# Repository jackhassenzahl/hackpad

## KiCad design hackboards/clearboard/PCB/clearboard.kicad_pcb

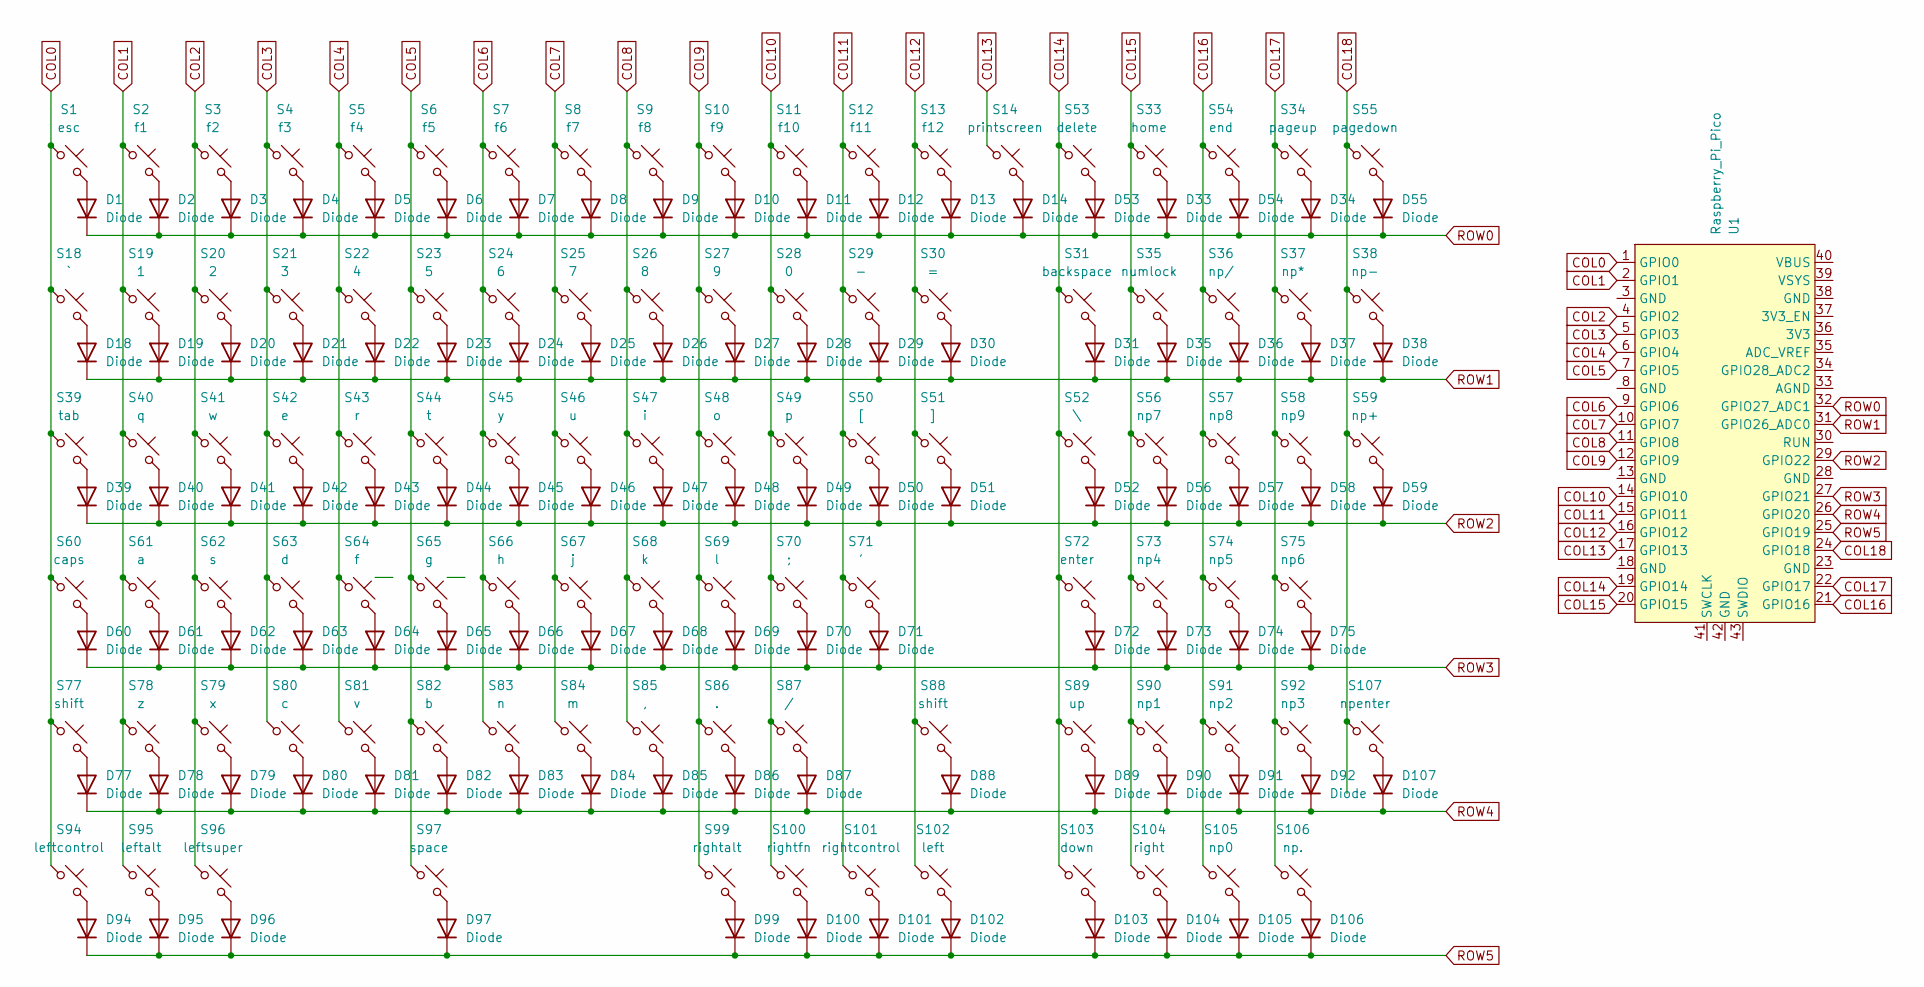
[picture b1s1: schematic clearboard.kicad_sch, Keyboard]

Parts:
D1, D2, D3, D4, D5, D6, D7, D8, D9, D10, D11, D12, D13, D14, D18, D19, D20, D21, D22, D23, D24, D25, D26, D27, D28, D29, D30, D31, D33, D34, D35, D36, D37, D38, D39, D40, D41, D42, D43, D44, D45, D46, D47, D48, D49, D50, D51, D52, D53, D54, D55, D56, D57, D58, D59, D60, D61, D62, D63, D64, D65, D66, D67, D68, D69, D70, D71, D72, D73, D74, D75, D77, D78, D79, D80, D81, D82, D83, D84, D85, D86, D87, D88, D89, D90, D91, D92, D94, D95, D96, D97, D99, D100, D101, D102, D103, D104, D105, D106, D107: Diode; Diode_DO-35
S1: esc; MX_PCB_1.00u
S2: f1; MX_PCB_1.00u
S3: f2; MX_PCB_1.00u
S4: f3; MX_PCB_1.00u
S5: f4; MX_PCB_1.00u
S6: f5; MX_PCB_1.00u
S7: f6; MX_PCB_1.00u
S8: f7; MX_PCB_1.00u
S9: f8; MX_PCB_1.00u
S10: f9; MX_PCB_1.00u
S11: f10; MX_PCB_1.00u
S12: f11; MX_PCB_1.00u
S13: f12; MX_PCB_1.00u
S14: printscreen; MX_PCB_1.00u
S18: `; MX_PCB_1.00u
S19: 1; MX_PCB_1.00u
S20: 2; MX_PCB_1.00u
S21: 3; MX_PCB_1.00u
S22: 4; MX_PCB_1.00u
S23: 5; MX_PCB_1.00u
S24: 6; MX_PCB_1.00u
S25: 7; MX_PCB_1.00u
S26: 8; MX_PCB_1.00u
S27: 9; MX_PCB_1.00u
S28: 0; MX_PCB_1.00u
S29: -; MX_PCB_1.00u
S30: =; MX_PCB_1.00u
S31: backspace; MX_PCB_2.00u
S33: home; MX_PCB_1.00u
S34: pageup; MX_PCB_1.00u
S35: numlock; MX_PCB_1.00u
S36: np/; MX_PCB_1.00u
S37: np*; MX_PCB_1.00u
S38: np-; MX_PCB_1.00u
S39: tab; MX_PCB_1.50u
S40: q; MX_PCB_1.00u
S41: w; MX_PCB_1.00u
S42: e; MX_PCB_1.00u
S43: r; MX_PCB_1.00u
S44: t; MX_PCB_1.00u
S45: y; MX_PCB_1.00u
S46: u; MX_PCB_1.00u
S47: i; MX_PCB_1.00u
S48: o; MX_PCB_1.00u
S49: p; MX_PCB_1.00u
S50: [; MX_PCB_1.00u
S51: ]; MX_PCB_1.00u
S52: \; MX_PCB_1.50u
S53: delete; MX_PCB_1.00u
S54: end; MX_PCB_1.00u
S55: pagedown; MX_PCB_1.00u
S56: np7; MX_PCB_1.00u
S57: np8; MX_PCB_1.00u
S58: np9; MX_PCB_1.00u
S59: np+; MX_PCB_2.00u_90deg
S60: caps; MX_PCB_1.75u
S61: a; MX_PCB_1.00u
S62: s; MX_PCB_1.00u
S63: d; MX_PCB_1.00u
S64: f; MX_PCB_1.00u
S65: g; MX_PCB_1.00u
S66: h; MX_PCB_1.00u
S67: j; MX_PCB_1.00u
S68: k; MX_PCB_1.00u
S69: l; MX_PCB_1.00u
S70: ;; MX_PCB_1.00u
S71: '; MX_PCB_1.00u
S72: enter; MX_PCB_2.25u
S73: np4; MX_PCB_1.00u
S74: np5; MX_PCB_1.00u
S75: np6; MX_PCB_1.00u
S77: shift; MX_PCB_2.25u
S78: z; MX_PCB_1.00u
S79: x; MX_PCB_1.00u
S80: c; MX_PCB_1.00u
S81: v; MX_PCB_1.00u
S82: b; MX_PCB_1.00u
S83: n; MX_PCB_1.00u
S84: m; MX_PCB_1.00u
S85: ,; MX_PCB_1.00u
S86: .; MX_PCB_1.00u
S87: /; MX_PCB_1.00u
S88: shift; MX_PCB_1.75u
S89: up; MX_PCB_1.00u
S90: np1; MX_PCB_1.00u
S91: np2; MX_PCB_1.00u
S92: np3; MX_PCB_1.00u
S94: leftcontrol; MX_Plate_1.25u
S95: leftalt; MX_Plate_1.25u
S96: leftsuper; MX_Plate_1.25u
S97: space; MX_PCB_6.25u
S99: rightalt; MX_PCB_1.00u
S100: rightfn; MX_PCB_1.00u
S101: rightcontrol; MX_PCB_1.00u
S102: left; MX_PCB_1.00u
S103: down; MX_PCB_1.00u
S104: right; MX_PCB_1.00u
S105: np0; MX_PCB_1.00u
S106: np.; MX_PCB_1.00u
S107: npenter; MX_PCB_2.00u_90deg
U1: Raspberry_Pi_Pico

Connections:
COL0: S1.1, S18.1, S39.1, S60.1, S77.1, S94.1, U1.1 (GPIO0)
COL1: S2.1, S19.1, S40.1, S61.1, S78.1, S95.1, U1.2 (GPIO1)
COL2: S3.1, S20.1, S41.1, S62.1, S79.1, S96.1, U1.4 (GPIO2)
COL3: S4.1, S21.1, S42.1, S63.1, S80.1, U1.5 (GPIO3)
COL4: S5.1, S22.1, S43.1, S64.1, S81.1, U1.6 (GPIO4)
COL5: S6.1, S23.1, S44.1, S65.1, S82.1, S97.1, U1.7 (GPIO5)
COL6: S7.1, S24.1, S45.1, S66.1, S83.1, U1.9 (GPIO6)
COL7: S8.1, S25.1, S46.1, S67.1, S84.1, U1.10 (GPIO7)
COL8: S9.1, S26.1, S47.1, S68.1, S85.1, U1.11 (GPIO8)
COL9: S10.1, S27.1, S48.1, S69.1, S86.1, S99.1, U1.12 (GPIO9)
COL10: S11.1, S28.1, S49.1, S70.1, S87.1, S100.1, U1.14 (GPIO10)
COL11: S12.1, S29.1, S50.1, S71.1, S101.1, U1.15 (GPIO11)
COL12: S13.1, S30.1, S51.1, S88.1, S102.1, U1.16 (GPIO12)
COL13: S14.1, U1.17 (GPIO13)
COL14: S31.1, S52.1, S53.1, S72.1, S89.1, S103.1, U1.19 (GPIO14)
COL15: S33.1, S35.1, S56.1, S73.1, S90.1, S104.1, U1.20 (GPIO15)
COL16: S36.1, S54.1, S57.1, S74.1, S91.1, S105.1, U1.21 (GPIO16)
COL17: S34.1, S37.1, S58.1, S75.1, S92.1, S106.1, U1.22 (GPIO17)
COL18: S38.1, S55.1, S59.1, S107.1, U1.24 (GPIO18)
unnamed: D1.2 (A), S1.2
unnamed: D2.2 (A), S2.2
unnamed: D3.2 (A), S3.2
unnamed: D4.2 (A), S4.2
unnamed: D5.2 (A), S5.2
unnamed: D6.2 (A), S6.2
unnamed: D7.2 (A), S7.2
unnamed: D8.2 (A), S8.2
unnamed: D9.2 (A), S9.2
unnamed: D10.2 (A), S10.2
unnamed: D11.2 (A), S11.2
unnamed: D12.2 (A), S12.2
unnamed: D13.2 (A), S13.2
unnamed: D14.2 (A), S14.2
unnamed: D18.2 (A), S18.2
unnamed: D19.2 (A), S19.2
unnamed: D20.2 (A), S20.2
unnamed: D21.2 (A), S21.2
unnamed: D22.2 (A), S22.2
unnamed: D23.2 (A), S23.2
unnamed: D24.2 (A), S24.2
unnamed: D25.2 (A), S25.2
unnamed: D26.2 (A), S26.2
unnamed: D27.2 (A), S27.2
unnamed: D28.2 (A), S28.2
unnamed: D29.2 (A), S29.2
unnamed: D30.2 (A), S30.2
unnamed: D31.2 (A), S31.2
unnamed: D33.2 (A), S33.2
unnamed: D34.2 (A), S34.2
unnamed: D35.2 (A), S35.2
unnamed: D36.2 (A), S36.2
unnamed: D37.2 (A), S37.2
unnamed: D38.2 (A), S38.2
unnamed: D39.2 (A), S39.2
unnamed: D40.2 (A), S40.2
unnamed: D41.2 (A), S41.2
unnamed: D42.2 (A), S42.2
unnamed: D43.2 (A), S43.2
unnamed: D44.2 (A), S44.2
unnamed: D45.2 (A), S45.2
unnamed: D46.2 (A), S46.2
unnamed: D47.2 (A), S47.2
unnamed: D48.2 (A), S48.2
unnamed: D49.2 (A), S49.2
unnamed: D50.2 (A), S50.2
unnamed: D51.2 (A), S51.2
unnamed: D52.2 (A), S52.2
unnamed: D53.2 (A), S53.2
unnamed: D54.2 (A), S54.2
unnamed: D55.2 (A), S55.2
unnamed: D56.2 (A), S56.2
unnamed: D57.2 (A), S57.2
unnamed: D58.2 (A), S58.2
unnamed: D59.2 (A), S59.2
unnamed: D60.2 (A), S60.2
unnamed: D61.2 (A), S61.2
unnamed: D62.2 (A), S62.2
unnamed: D63.2 (A), S63.2
unnamed: D64.2 (A), S64.2
unnamed: D65.2 (A), S65.2
unnamed: D66.2 (A), S66.2
unnamed: D67.2 (A), S67.2
unnamed: D68.2 (A), S68.2
unnamed: D69.2 (A), S69.2
unnamed: D70.2 (A), S70.2
unnamed: D71.2 (A), S71.2
unnamed: D72.2 (A), S72.2
unnamed: D73.2 (A), S73.2
unnamed: D74.2 (A), S74.2
unnamed: D75.2 (A), S75.2
unnamed: D77.2 (A), S77.2
unnamed: D78.2 (A), S78.2
unnamed: D79.2 (A), S79.2
unnamed: D80.2 (A), S80.2
unnamed: D81.2 (A), S81.2
unnamed: D82.2 (A), S82.2
unnamed: D83.2 (A), S83.2
unnamed: D84.2 (A), S84.2
unnamed: D85.2 (A), S85.2
unnamed: D86.2 (A), S86.2
unnamed: D87.2 (A), S87.2
unnamed: D88.2 (A), S88.2
unnamed: D89.2 (A), S89.2
unnamed: D90.2 (A), S90.2
unnamed: D91.2 (A), S91.2
unnamed: D92.2 (A), S92.2
unnamed: D94.2 (A), S94.2
unnamed: D95.2 (A), S95.2
unnamed: D96.2 (A), S96.2
unnamed: D97.2 (A), S97.2
unnamed: D99.2 (A), S99.2
unnamed: D100.2 (A), S100.2
unnamed: D101.2 (A), S101.2
unnamed: D102.2 (A), S102.2
unnamed: D103.2 (A), S103.2
unnamed: D104.2 (A), S104.2
unnamed: D105.2 (A), S105.2
unnamed: D106.2 (A), S106.2
unnamed: D107.2 (A), S107.2
ROW0: D1.1 (K), D2.1 (K), D3.1 (K), D4.1 (K), D5.1 (K), D6.1 (K), D7.1 (K), D8.1 (K), D9.1 (K), D10.1 (K), D11.1 (K), D12.1 (K), D13.1 (K), D14.1 (K), D33.1 (K), D34.1 (K), D53.1 (K), D54.1 (K), D55.1 (K), U1.32 (GPIO27_ADC1)
ROW1: D18.1 (K), D19.1 (K), D20.1 (K), D21.1 (K), D22.1 (K), D23.1 (K), D24.1 (K), D25.1 (K), D26.1 (K), D27.1 (K), D28.1 (K), D29.1 (K), D30.1 (K), D31.1 (K), D35.1 (K), D36.1 (K), D37.1 (K), D38.1 (K), U1.31 (GPIO26_ADC0)
ROW2: D39.1 (K), D40.1 (K), D41.1 (K), D42.1 (K), D43.1 (K), D44.1 (K), D45.1 (K), D46.1 (K), D47.1 (K), D48.1 (K), D49.1 (K), D50.1 (K), D51.1 (K), D52.1 (K), D56.1 (K), D57.1 (K), D58.1 (K), D59.1 (K), U1.29 (GPIO22)
ROW3: D60.1 (K), D61.1 (K), D62.1 (K), D63.1 (K), D64.1 (K), D65.1 (K), D66.1 (K), D67.1 (K), D68.1 (K), D69.1 (K), D70.1 (K), D71.1 (K), D72.1 (K), D73.1 (K), D74.1 (K), D75.1 (K), U1.27 (GPIO21)
ROW4: D77.1 (K), D78.1 (K), D79.1 (K), D80.1 (K), D81.1 (K), D82.1 (K), D83.1 (K), D84.1 (K), D85.1 (K), D86.1 (K), D87.1 (K), D88.1 (K), D89.1 (K), D90.1 (K), D91.1 (K), D92.1 (K), D107.1 (K), U1.26 (GPIO20)
ROW5: D94.1 (K), D95.1 (K), D96.1 (K), D97.1 (K), D99.1 (K), D100.1 (K), D101.1 (K), D102.1 (K), D103.1 (K), D104.1 (K), D105.1 (K), D106.1 (K), U1.25 (GPIO19)

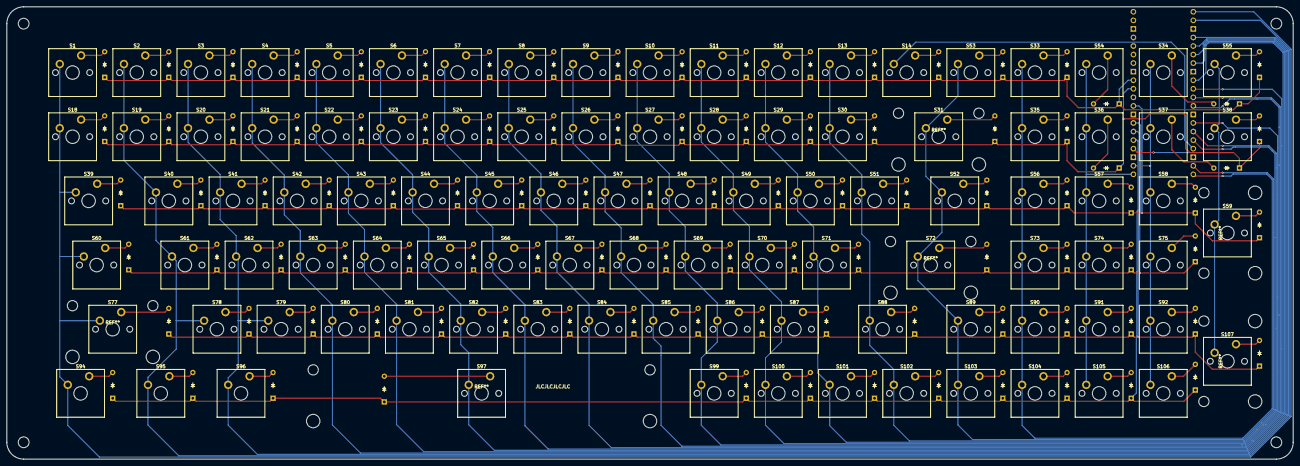
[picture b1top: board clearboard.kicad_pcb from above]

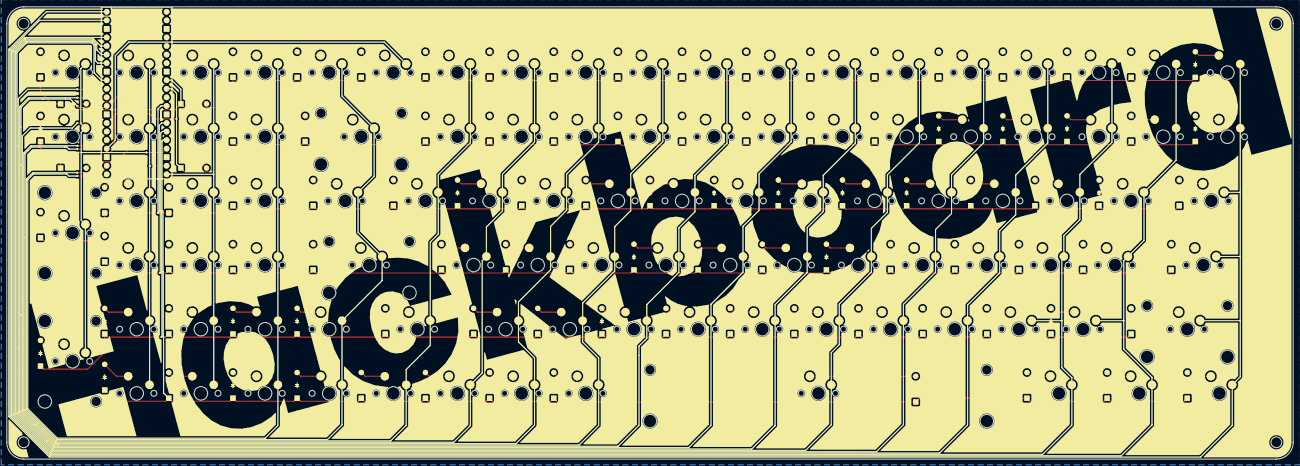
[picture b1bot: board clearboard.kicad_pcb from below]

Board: 2 copper layers, 381.9 x 134.3 mm, 201 parts (101 on the bottom side), 125 nets.

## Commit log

2025-03-07 added readme and added keyboard files
2025-03-07 made update and renamed old files
2025-03-07 updated kicad and that did things i guess
2025-03-25 changed keyboard name
2025-03-25 renamed to openboard
2025-03-27 did stuff
2025-03-27 JUST WORK
2025-03-27 something changed after I pulled idk
2025-04-01 renamed for the last time to clearboard
2025-04-01 updated firmware
2025-04-18 I think I finalized my pcb
